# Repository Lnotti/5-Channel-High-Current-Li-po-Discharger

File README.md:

# 5 Channel High Current LiPo Storage Discharger

A PCB designed to discharge 6S LiHV battery packs to storage voltage (3.8V per cell / 22.8V total) across up to 5 independent channels simultaneously.

## Overview

Leaving LiPo packs fully charged for extended periods degrades cell chemistry over time. This board solves that by providing a dedicated, controlled way to bring packs down to storage voltage after a flying session without needing a full featured charger to do it.

Each of the 5 channels accepts a 6S pack via an XT60 connector and independently discharges it to 22.8V, cutting off automatically when the target is reached. Channels are fully isolated from each other so packs at different voltages can be discharged simultaneously without risk.

## Problems with current solutions

I have a lipo charger that doubles as a lipo discharger, but it falls short in many aspects.
- Cost ($100+)
- Only two channels
- Discharge current only 0.2A max
- Slows down immensely close to the end of discharge cycle

I also have small lipo discharger that clip onto individual packs that also fall short
- Takes 3+ hours to discharge to storage
- Only has a light to let me know that it has finished (I forget about them since they are so small)
- High leakage current
- High leakage current combined with the time taken to discharge combined with their forgettability leads to frequent overdischarging making me plug them back in to charge ruining the ease

## Status

Version 0.1.1 is a complete board redesign addressing multiple hardware issues identified during review of the 0.1.0 prototype. The revised board has been submitted for manufacture. Testing and firmware development are ongoing.

## Hardware

- STM32F103C8T6 microcontroller
- Active MOSFET load per channel with wirewound power resistors
- Buck converter and 3.3V LDO onboard power supply
- USB-C port for firmware flashing via DFU bootloader
- Active cooling via 40mm 5V fan
- Power status LED for supply rail debugging
- SWD header for live debugging
- Multiple STM32 connectivity options: USB, I2C, ST-Link, UART, DFU

## Specifications

- Input: 6S LiHV (22.8V - 26.1V)
- Channels: 5 independent
- Discharge current: approximately 1A per channel
- Target storage voltage: 22.8V (3.8V per cell)
- Connector: XT60 female PCB mount
- Board dimensions: 160 x 110mm

## Version History

### v0.1.1 — Complete Board Redesign
*Current version*

A full redesign addressing hardware errors found during schematic and layout review of v0.1.0.

**Bug fixes:**
- Corrected footprints for large wirewound power resistors which were wrong in v0.1.0
- Fixed STM32F103C8T6 footprint which was incorrect in v0.1.0
- Replaced buck converter with a higher rated part after identifying that the original selection would be insufficient for LiHV pack voltages (26.1V max vs 25.2V assumed for standard LiPo)
- Updated voltage divider resistor values (1M / 120k) to bring the ADC sense voltage within safe range for LiHV full charge voltage — previous values would have exceeded the STM32 3.3V ADC input limit at 26.1V
- Updated voltage dividers to higher values to reduce current draw, as to not discharge batteries less than their storage voltage after discharging process is complete.

**Design changes:**
- Discharge resistors repositioned to the center of the board based on thermal simulation results for improved heat distribution
- Removed per-channel RGB LEDs to simplify bring-up and reduce scope; power system debugging is now the immediate priority
- Added power rail status LED to aid debugging of the onboard supply
- Added multiple STM32 connectivity options: USB, I2C, ST-Link, UART, DFU headers
- Removed oversized battery net traces; 1A continuous current does not require large copper pours
- Redesigned discharge channels using hierarchical sheets for layout uniformity across all 5 channels and easier future edits
- General board layout cleanup and component alignment

**Known limitations:**
- RGB per-channel status LEDs removed; may be reintroduced in a later revision once core functionality is validated
- Unsure of how precise the mosfet discharge current in relation to gate voltage will be, this may create issues with precision at the end of a discharge cycle limiting speed.
- Firmware development not yet started
- Unsure of what control loop I will use to handle getting to storage voltage at a consistent current with no overshoot

---

### v0.1.0 — Initial Prototype
*First PCB submission. Multiple hardware errors identified prior to and during bring-up.*

- Initial 5-channel discharge board design
- STM32F103C8T6 microcontroller
- PCA9685 16 channel PWM driver for RGB status LEDs
- Per channel RGB status LED
- USB-C DFU bootloader
- SWD debug header
- 160 x 110mm board

**Issues identified:**
- Wrong footprints for wirewound power resistors
- Wrong STM32 footprint
- Buck converter underrated for LiHV input voltage
- Voltage divider ratio unsafe for LiHV full charge voltage on STM32 ADC
- Board layout not uniform across discharge channels

---

## Planned Revisions

- Case design with integrated fan mounting and ventilation
- Thermal testing and validation on physical hardware
- Firmware development and testing
- Potential reintroduction of per-channel RGB status LEDs
- Potential support for additional cell counts
- Further refinement based on prototype testing results

## Repository Contents

- KiCad schematic and PCB layout files
- Gerber files for manufacture
- Bill of materials

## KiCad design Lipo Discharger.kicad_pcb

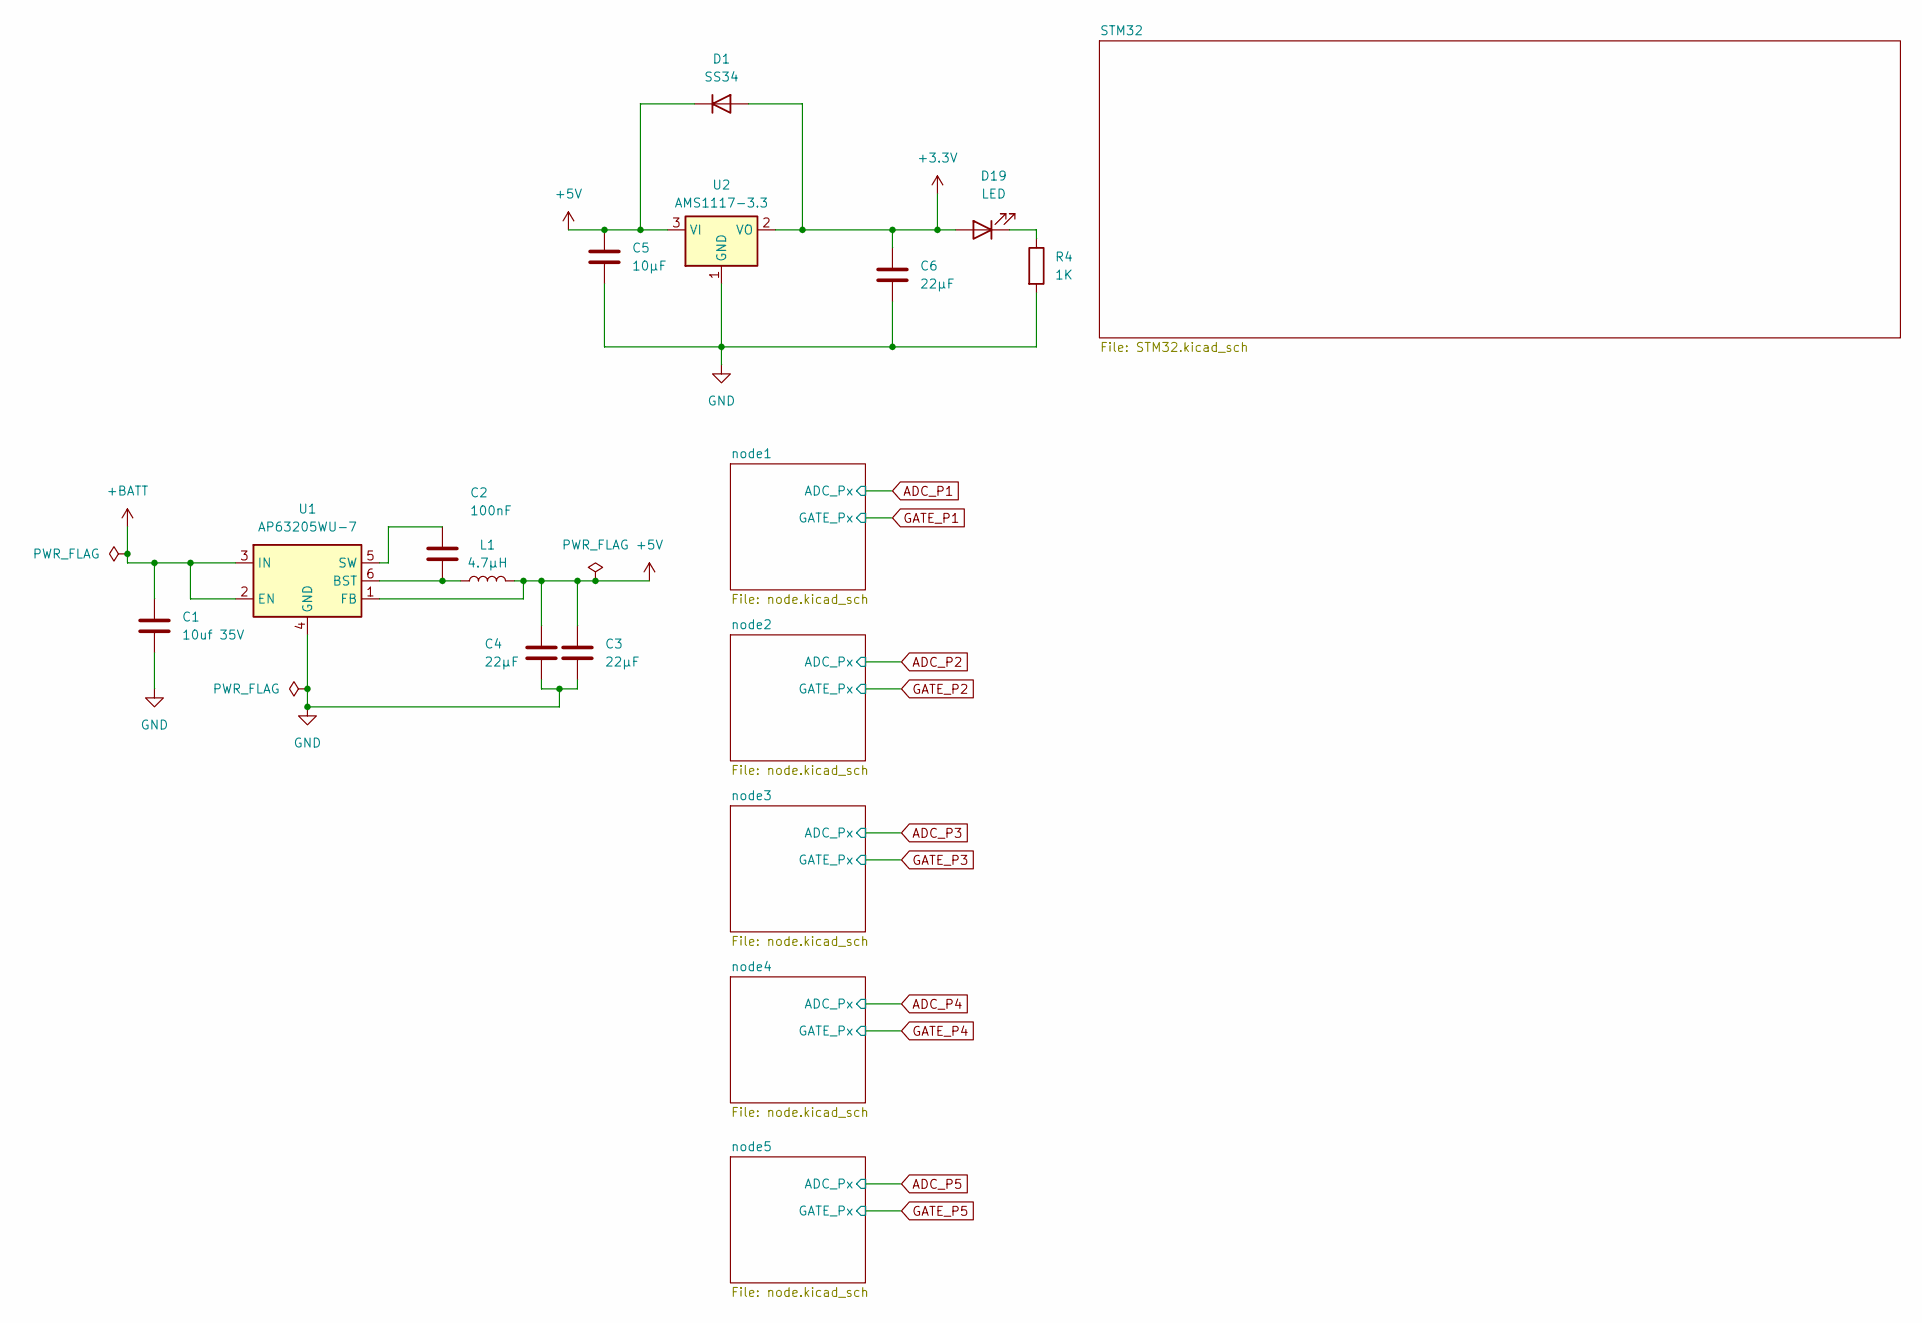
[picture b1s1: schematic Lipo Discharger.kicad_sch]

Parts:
C1: 10uf 35V; C_0805_2012Metric_Pad1.18x1.45mm_HandSolder
C2: 100nF; C_0805_2012Metric_Pad1.18x1.45mm_HandSolder
C3, C4, C6: 22µF; C_0805_2012Metric_Pad1.18x1.45mm_HandSolder
C5: 10µF; C_0805_2012Metric_Pad1.18x1.45mm_HandSolder
D1: SS34; D_SMB_Handsoldering
D19: LED; LED_2010_5025Metric_Pad1.52x2.65mm_HandSolder
L1: 4.7µH; L_7.3x7.3_H4.5
R4: 1K; R_0805_2012Metric_Pad1.20x1.40mm_HandSolder
U1: AP63205WU-7; TSOT-23-6
U2: AMS1117-3.3; SOT-223-3_TabPin2

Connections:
+3.3V: C6.1, D1.2 (A), D19.2 (A), U2.2 (VO); also elsewhere on the board
+5V: C3.1, C4.1, C5.1, D1.1 (K), L1.2, U1.1 (FB), U2.3 (VI); also elsewhere on the board
+BATT: C1.1, U1.2 (EN), U1.3 (IN); also elsewhere on the board
GND: C1.2, C3.2, C4.2, C5.2, C6.2, R4.2, U1.4 (GND), U2.1 (GND); also elsewhere on the board
unnamed: D19.1 (K), R4.1
unnamed: C2.2, L1.1, U1.6 (BST)
unnamed: C2.1, U1.5 (SW)

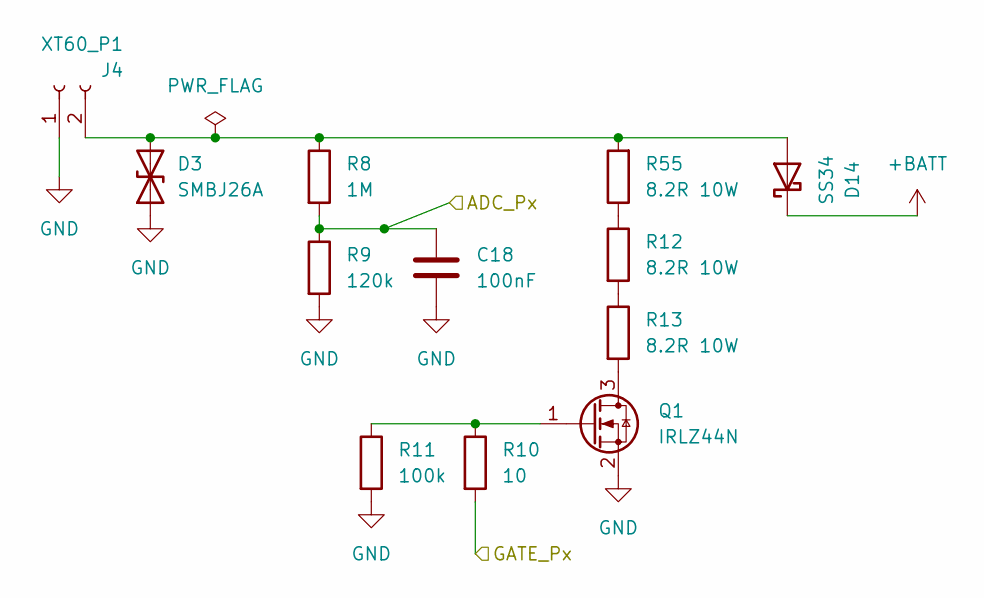
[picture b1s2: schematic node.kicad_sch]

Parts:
C18: 100nF; C_0805_2012Metric_Pad1.18x1.45mm_HandSolder
D3: SMBJ26A; D_SMB_Handsoldering
D14: SS34; D_SMA
J4: XT60_P1; AMASS_XT60PW-M_1x02_P7.20mm_Horizontal
Q1: IRLZ44N; TO-220-3_Vertical
R8: 1M; R_0805_2012Metric_Pad1.20x1.40mm_HandSolder
R9: 120k; R_0805_2012Metric_Pad1.20x1.40mm_HandSolder
R10: 10; R_0805_2012Metric_Pad1.20x1.40mm_HandSolder
R11: 100k; R_0805_2012Metric_Pad1.20x1.40mm_HandSolder
R12, R13, R55: 8.2R 10W; R_Axial_Power_L38.0mm_W6.4mm_P45.72mm

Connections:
+BATT: D14.1 (K); also elsewhere on the board
ADC_P1: C18.1, R8.2, R9.1; also elsewhere on the board
GATE_P1: R10.2; also elsewhere on the board
GND: C18.2, D3.1 (A1), J4.1, Q1.2 (S), R9.2, R11.2; also elsewhere on the board
unnamed: D3.2 (A2), D14.2 (A), J4.2, R8.1, R55.2
unnamed: Q1.3 (D), R13.2
unnamed: Q1.1 (G), R10.1, R11.1
unnamed: R12.1, R55.1
unnamed: R12.2, R13.1

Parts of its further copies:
C19, C20, C21, C22: 100nF; C_0805_2012Metric_Pad1.18x1.45mm_HandSolder
D4, D5, D6, D7: SMBJ26A; D_SMB_Handsoldering
D15, D16, D17, D18: SS34; D_SMA
J5, J6, J7, J8: XT60_P1; AMASS_XT60PW-M_1x02_P7.20mm_Horizontal
Q2, Q3, Q4, Q5: IRLZ44N; TO-220-3_Vertical
R14, R20, R26, R32: 1M; R_0805_2012Metric_Pad1.20x1.40mm_HandSolder
R15, R21, R27, R33: 120k; R_0805_2012Metric_Pad1.20x1.40mm_HandSolder
R16, R22, R28, R34: 100k; R_0805_2012Metric_Pad1.20x1.40mm_HandSolder
R17, R23, R29, R35: 10; R_0805_2012Metric_Pad1.20x1.40mm_HandSolder
R18, R19, R24, R25, R30, R31, R36, R37, R56, R57, R58, R59: 8.2R 10W; R_Axial_Power_L38.0mm_W6.4mm_P45.72mm

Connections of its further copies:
+BATT: D15.1 (K), D16.1 (K), D17.1 (K), D18.1 (K); also elsewhere on the board
ADC_P2: C19.1, R14.2, R15.1; also elsewhere on the board
ADC_P3: C20.1, R20.2, R21.1; also elsewhere on the board
ADC_P4: C21.1, R26.2, R27.1; also elsewhere on the board
ADC_P5: C22.1, R32.2, R33.1; also elsewhere on the board
GATE_P2: R17.2; also elsewhere on the board
GATE_P3: R23.2; also elsewhere on the board
GATE_P4: R29.2; also elsewhere on the board
GATE_P5: R35.2; also elsewhere on the board
GND: C19.2, C20.2, C21.2, C22.2, D4.1 (A1), D5.1 (A1), D6.1 (A1), D7.1 (A1), J5.1, J6.1, J7.1, J8.1, Q2.2 (S), Q3.2 (S), Q4.2 (S), Q5.2 (S), R15.2, R16.2, R21.2, R22.2, R27.2, R28.2, R33.2, R34.2; also elsewhere on the board
unnamed: D4.2 (A2), D15.2 (A), J5.2, R14.1, R56.2
unnamed: D5.2 (A2), D16.2 (A), J6.2, R20.1, R57.2
unnamed: D6.2 (A2), D17.2 (A), J7.2, R26.1, R58.2
unnamed: D7.2 (A2), D18.2 (A), J8.2, R32.1, R59.2
unnamed: Q2.3 (D), R19.2
unnamed: Q2.1 (G), R16.1, R17.1
unnamed: Q3.3 (D), R25.2
unnamed: Q3.1 (G), R22.1, R23.1
unnamed: Q4.3 (D), R31.2
unnamed: Q4.1 (G), R28.1, R29.1
unnamed: Q5.3 (D), R37.2
unnamed: Q5.1 (G), R34.1, R35.1
unnamed: R18.1, R56.1
unnamed: R18.2, R19.1
unnamed: R24.1, R57.1
unnamed: R24.2, R25.1
unnamed: R30.1, R58.1
unnamed: R30.2, R31.1
unnamed: R36.1, R59.1
unnamed: R36.2, R37.1

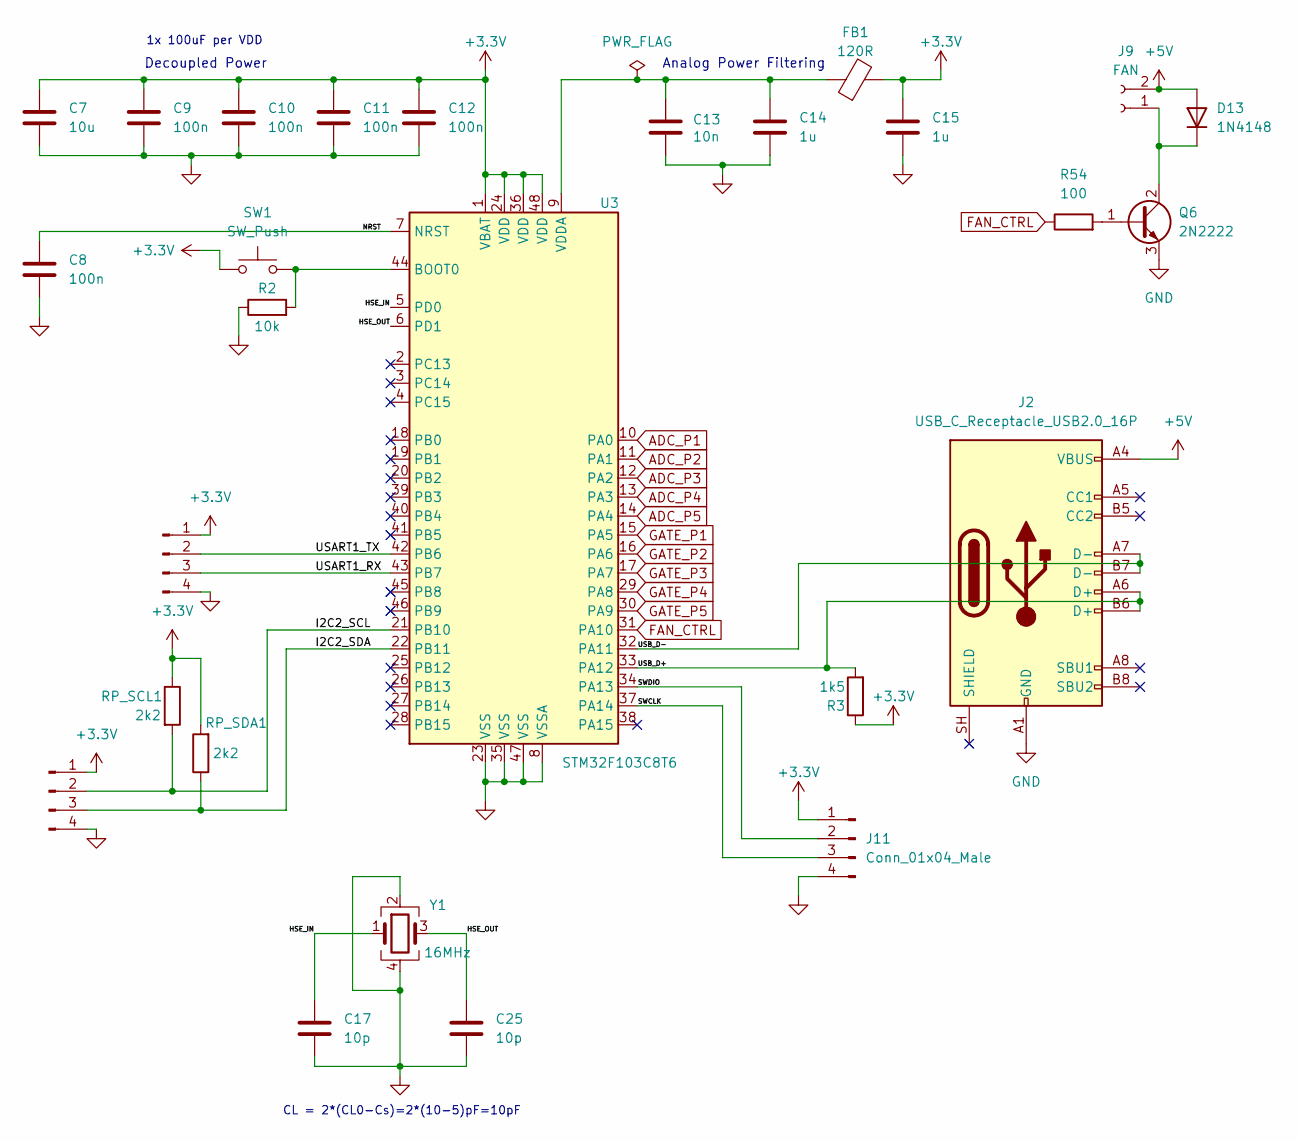
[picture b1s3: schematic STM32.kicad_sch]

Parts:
C7: 10u; C_0603_1608Metric
C8, C9, C10, C11, C12: 100n; C_0402_1005Metric
C13: 10n; C_0402_1005Metric
C14, C15: 1u; C_0402_1005Metric
C17, C25: 10p; C_0402_1005Metric
D13: 1N4148; D_DO-35_SOD27_P7.62mm_Horizontal
FB1: 120R; L_0603_1608Metric
J1, J3, J11: Conn_01x04_Male; PinHeader_1x04_P2.00mm_Vertical
J2: USB_C_Receptacle_USB2.0_16P; USB_C_Receptacle_HRO_TYPE-C-31-M-12
J9: FAN; PinHeader_1x02_P2.54mm_Vertical
Q6: 2N2222; TO-92_Inline
R2: 10k; R_0402_1005Metric
R3: 1k5; R_0402_1005Metric
R54: 100; R_0805_2012Metric_Pad1.20x1.40mm_HandSolder
RP_SCL1: 2k2; R_0402_1005Metric
RP_SDA1: 2k2; R_0402_1005Metric
SW1: SW_Push; SW_PUSH_6mm
U3: STM32F103C8T6; LQFP-48_7x7mm_P0.5mm
Y1: 16MHz; Crystal_SMD_3225-4Pin_3.2x2.5mm

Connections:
+3.3V: C7.1, C9.1, C10.1, C11.1, C12.1, C15.1, FB1.2, J1.1, J3.1, J11.1, R3.1, RP_SCL1.1, RP_SDA1.2, SW1.1, U3.1 (VBAT), U3.24 (VDD), U3.36 (VDD), U3.48 (VDD); also elsewhere on the board
+5V: D13.2 (A), J2.A4 (VBUS), J2.A9 (VBUS), J2.B4 (VBUS), J2.B9 (VBUS), J9.2; also elsewhere on the board
/STM32/HSE_IN: C17.1, U3.5 (PD0), Y1.1
/STM32/HSE_OUT: C25.1, U3.6 (PD1), Y1.3
/STM32/I2C2_SCL: J3.2, RP_SCL1.2, U3.21 (PB10); also elsewhere on the board
/STM32/I2C2_SDA: J3.3, RP_SDA1.1, U3.22 (PB11); also elsewhere on the board
/STM32/NRST: C8.1, U3.7 (NRST)
/STM32/SWCLK: J11.3, U3.37 (PA14); also elsewhere on the board
/STM32/SWDIO: J11.2, U3.34 (PA13); also elsewhere on the board
/STM32/USART1_RX: J1.3, U3.43 (PB7); also elsewhere on the board
/STM32/USART1_TX: J1.2, U3.42 (PB6); also elsewhere on the board
/STM32/USB_D+: J2.A6 (D+), J2.B6 (D+), R3.2, U3.33 (PA12)
/STM32/USB_D-: J2.A7 (D-), J2.B7 (D-), U3.32 (PA11)
ADC_P1: U3.10 (PA0); also elsewhere on the board
ADC_P2: U3.11 (PA1); also elsewhere on the board
ADC_P3: U3.12 (PA2); also elsewhere on the board
ADC_P4: U3.13 (PA3); also elsewhere on the board
ADC_P5: U3.14 (PA4); also elsewhere on the board
FAN_CTRL: R54.1, U3.31 (PA10)
GATE_P1: U3.15 (PA5); also elsewhere on the board
GATE_P2: U3.16 (PA6); also elsewhere on the board
GATE_P3: U3.17 (PA7); also elsewhere on the board
GATE_P4: U3.29 (PA8); also elsewhere on the board
GATE_P5: U3.30 (PA9); also elsewhere on the board
GND: C7.2, C8.2, C9.2, C10.2, C11.2, C12.2, C13.2, C14.2, C15.2, C17.2, C25.2, J1.4, J2.A1 (GND), J2.A12 (GND), J2.B1 (GND), J2.B12 (GND), J3.4, J11.4, Q6.3 (E), R2.1, U3.8 (VSSA), U3.23 (VSS), U3.35 (VSS), U3.47 (VSS), Y1.2, Y1.4; also elsewhere on the board
unnamed 26: D13.1 (K), J9.1, Q6.2 (C); also elsewhere on the board
unnamed: Q6.1 (B), R54.2
unnamed: R2.2, SW1.2, U3.44 (BOOT0)
unnamed: C13.1, C14.1, FB1.1, U3.9 (VDDA)

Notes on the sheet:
1x 100uF per VDD
Analog Power Filtering
Decoupled Power
CL = 2*(CL0-Cs)=2*(10-5)pF=10pF

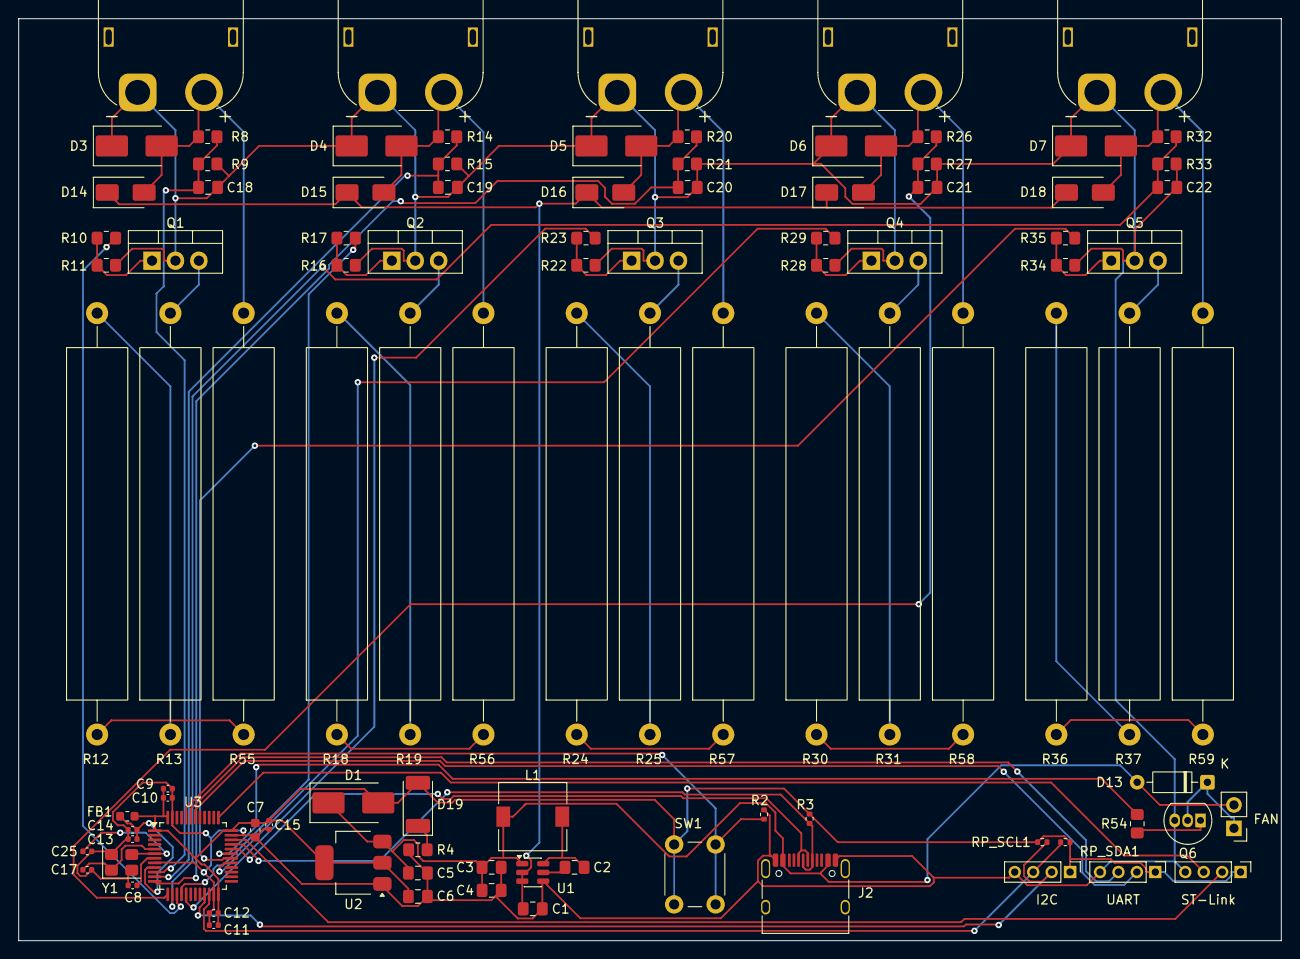
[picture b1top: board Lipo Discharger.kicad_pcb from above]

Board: 2 copper layers, 137.0 x 100.0 mm, 99 parts (0 on the bottom side), 58 nets.

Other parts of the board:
FAN: FAN; PinHeader_1x02_P2.54mm_Vertical
I2C: Conn_01x04_Male; PinHeader_1x04_P2.00mm_Vertical
ST-Link: Conn_01x04_Male; PinHeader_1x04_P2.00mm_Vertical
UART: Conn_01x04_Male; PinHeader_1x04_P2.00mm_Vertical

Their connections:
+3.3V: I2C.1, ST-Link.1, UART.1; also elsewhere on the board
+5V: FAN.2; also elsewhere on the board
/STM32/I2C2_SCL: I2C.2; also elsewhere on the board
/STM32/I2C2_SDA: I2C.3; also elsewhere on the board
/STM32/SWCLK: ST-Link.3; also elsewhere on the board
/STM32/SWDIO: ST-Link.2; also elsewhere on the board
/STM32/USART1_RX: UART.3; also elsewhere on the board
/STM32/USART1_TX: UART.2; also elsewhere on the board
GND: I2C.4, ST-Link.4, UART.4; also elsewhere on the board
unnamed 26: FAN.1; also elsewhere on the board

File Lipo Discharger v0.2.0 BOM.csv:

"Id";"Designator";"Footprint";"Quantity";"Designation";"Supplier and ref";
1;"C1";"C_0805_2012Metric_Pad1.18x1.45mm_HandSolder";1;"10uf 35V";;;
2;"C2, C18, C19, C20, C21, C22";"C_0805_2012Metric_Pad1.18x1.45mm_HandSolder";6;"100nF";;;
3;"C3, C4, C6";"C_0805_2012Metric_Pad1.18x1.45mm_HandSolder";3;"22µF";;;
4;"C5";"C_0805_2012Metric_Pad1.18x1.45mm_HandSolder";1;"10µF";;;
5;"C7";"C_0603_1608Metric";1;"10u";;;
6;"C8, C9, C10, C11, C12";"C_0402_1005Metric";5;"100n";;;
7;"C13";"C_0402_1005Metric";1;"10n";;;
8;"C14, C15";"C_0402_1005Metric";2;"1u";;;
9;"C17, C25";"C_0402_1005Metric";2;"10p";;;
10;"D1";"D_SMB_Handsoldering";1;"SS34";;;
11;"D3, D4, D5, D6, D7";"D_SMB_Handsoldering";5;"SMBJ26A";;;
12;"D13";"D_DO-35_SOD27_P7.62mm_Horizontal";1;"1N4148";;;
13;"D14, D15, D16, D17, D18";"D_SMA";5;"SS34";;;
14;"D19";"LED_2010_5025Metric_Pad1.52x2.65mm_HandSolder";1;"LED";;;
15;"FAN";"PinHeader_1x02_P2.54mm_Vertical";1;"FAN";;;
16;"FB1";"L_0603_1608Metric";1;"120R";;;
17;"I2C, ST-Link, UART";"PinHeader_1x04_P2.00mm_Vertical";3;"Conn_01x04_Male";;;
18;"J2";"USB_C_Receptacle_HRO_TYPE-C-31-M-12";1;"USB_C_Receptacle_USB2.0_16P";;;
19;"J4, J5, J6, J7, J8";"AMASS_XT60PW-M_1x02_P7.20mm_Horizontal";5;"XT60_P1";;;
20;"L1";"L_7.3x7.3_H4.5";1;"4.7µH";;;
21;"Q1, Q2, Q3, Q4, Q5";"TO-220-3_Vertical";5;"IRLZ44N";;;
22;"Q6";"TO-92_Inline";1;"2N2222";;;
23;"R2";"R_0402_1005Metric";1;"10k";;;
24;"R3";"R_0402_1005Metric";1;"1k5";;;
25;"R4";"R_0805_2012Metric_Pad1.20x1.40mm_HandSolder";1;"1K";;;
26;"R8, R14, R20, R26, R32";"R_0805_2012Metric_Pad1.20x1.40mm_HandSolder";5;"1M";;;
27;"R9, R15, R21, R27, R33";"R_0805_2012Metric_Pad1.20x1.40mm_HandSolder";5;"120k";;;
28;"R10, R17, R23, R29, R35";"R_0805_2012Metric_Pad1.20x1.40mm_HandSolder";5;"10";;;
29;"R11, R16, R22, R28, R34";"R_0805_2012Metric_Pad1.20x1.40mm_HandSolder";5;"100k";;;
30;"R12, R13, R18, R19, R24, R25, R30, R31, R36, R37, R55, R56, R57, R58, R59";"R_Axial_Power_L38.0mm_W6.4mm_P45.72mm";15;"8.2R 10W";;;
31;"R54";"R_0805_2012Metric_Pad1.20x1.40mm_HandSolder";1;"100";;;
32;"RP_SCL1, RP_SDA1";"R_0402_1005Metric";2;"2k2";;;
33;"SW1";"SW_PUSH_6mm";1;"SW_Push";;;
34;"U1";"TSOT-23-6";1;"AP63205WU-7";;;
35;"U2";"SOT-223-3_TabPin2";1;"AMS1117-3.3";;;
36;"U3";"LQFP-48_7x7mm_P0.5mm";1;"STM32F103C8T6";;;
37;"Y1";"Crystal_SMD_3225-4Pin_3.2x2.5mm";1;"16MHz";;;

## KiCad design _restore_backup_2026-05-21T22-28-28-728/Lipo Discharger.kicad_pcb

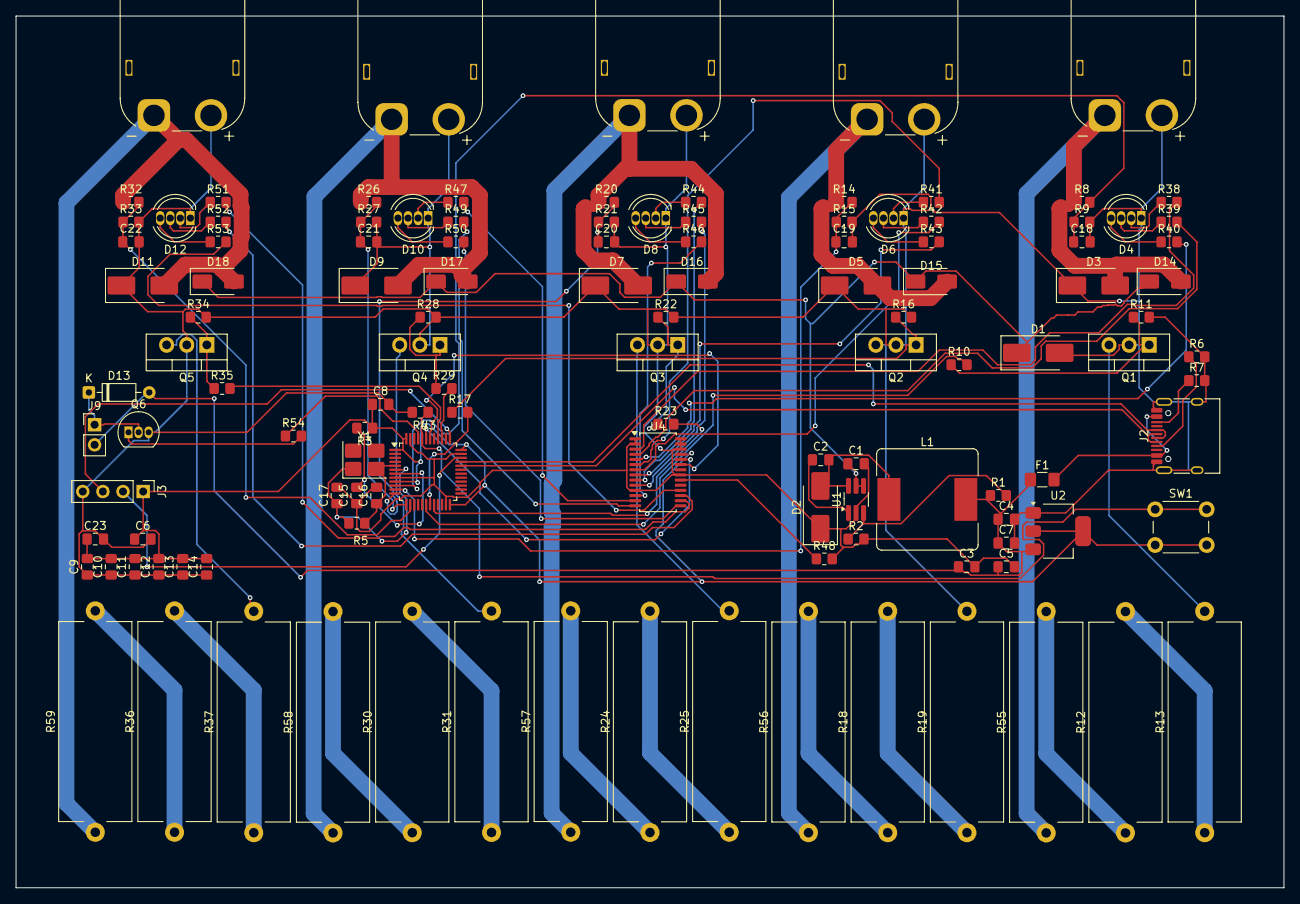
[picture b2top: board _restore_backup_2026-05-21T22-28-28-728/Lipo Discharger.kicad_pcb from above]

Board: 2 copper layers, 160.0 x 110.0 mm, 122 parts (0 on the bottom side), 89 nets.

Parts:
C1: 10uf 35V; C_0805_2012Metric_Pad1.18x1.45mm_HandSolder
C2, C7, C8, C9, C10, C11, C12, C15, C18, C19, C20, C21, C22, C23: 100nF; C_0805_2012Metric_Pad1.18x1.45mm_HandSolder
C3, C4: 22uF 10V; C_0805_2012Metric_Pad1.18x1.45mm_HandSolder
C5, C6: 10uF; C_0805_2012Metric_Pad1.18x1.45mm_HandSolder
C13: 1uF; C_0805_2012Metric_Pad1.18x1.45mm_HandSolder
C14: 10nF; C_0805_2012Metric_Pad1.18x1.45mm_HandSolder
C16, C17: 20pF; C_0805_2012Metric_Pad1.18x1.45mm_HandSolder
D1: D_TVS; D_SMB_Handsoldering
D2: SS34; D_SMB_Handsoldering
D3, D5, D7, D9, D11: SMBJ26A; D_SMB_Handsoldering
D4, D6, D8, D10, D12: LED_KRGB; LED_D5.0mm-4_RGB
D13: 1N4148; D_DO-35_SOD27_P7.62mm_Horizontal
D14, D15, D16, D17, D18: SS34; D_SMA
F1: Polyfuse; Fuse_1206_3216Metric_Pad1.42x1.75mm_HandSolder
J2: USB_C_Receptacle_USB2.0_16P; USB_C_Receptacle_HRO_TYPE-C-31-M-12
J3: SWD; PinHeader_1x04_P2.54mm_Vertical
J4: XT60_P1; AMASS_XT60PW-M_1x02_P7.20mm_Horizontal
J5: XT60_P2; AMASS_XT60PW-M_1x02_P7.20mm_Horizontal
J6: XT60_P3; AMASS_XT60PW-M_1x02_P7.20mm_Horizontal
J7: XT60_P4; AMASS_XT60PW-M_1x02_P7.20mm_Horizontal
J8: XT60_P5; AMASS_XT60PW-M_1x02_P7.20mm_Horizontal
J9: FAN; PinHeader_1x02_P2.54mm_Vertical
L1: 22uH; L_Bourns_SRR1260
Q1, Q2, Q3, Q4, Q5: IRLZ44N; TO-220-3_Vertical
Q6: 2N2222; TO-92_Inline
R1, R8, R11, R14, R16, R20, R22, R26, R28, R32, R34: 100k; R_0805_2012Metric_Pad1.20x1.40mm_HandSolder
R2: 20k; R_0805_2012Metric_Pad1.20x1.40mm_HandSolder
R3, R4, R48: 10k; R_0805_2012Metric_Pad1.20x1.40mm_HandSolder
R5: 1M; R_0805_2012Metric_Pad1.20x1.40mm_HandSolder
R6, R7: 5.1k; R_0805_2012Metric_Pad1.20x1.40mm_HandSolder
R9, R15, R21, R27, R33: 15k; R_0805_2012Metric_Pad1.20x1.40mm_HandSolder
R10, R17, R23, R29, R35: 10; R_0805_2012Metric_Pad1.20x1.40mm_HandSolder
R12, R13, R18, R19, R24, R25, R30, R31, R36, R37, R55, R56, R57, R58, R59: 8.2R 10W; R_Axial_Power_L25.0mm_W9.0mm_P27.94mm
R38, R41, R44, R47, R51: 68; R_0805_2012Metric_Pad1.20x1.40mm_HandSolder
R39, R40, R42, R43, R45, R46, R49, R50, R52, R53: 22; R_0805_2012Metric_Pad1.20x1.40mm_HandSolder
R54: 100; R_0805_2012Metric_Pad1.20x1.40mm_HandSolder
SW1: BOOT0_BTN; SW_PUSH_6mm
U1: MP2359DJ-LF-Z; TSOT-23-6_HandSoldering
U2: AMS1117-3.3; SOT-223-3_TabPin2
U3: STM32F103C8Tx; LQFP-48_7x7mm_P0.5mm
U4: PCA9685BS; TSSOP-28_4.4x9.7mm_P0.65mm
Y1: 8MHz; Crystal_SMD_3225-4Pin_3.2x2.5mm_HandSoldering

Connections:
+3.3V: C6.1, C8.1, C9.2, C10.2, C11.2, C12.2, C13.2, C14.2, C23.1, J3.1, R3.1, SW1.2, U2.2 (VO), U3.1 (VBAT), U3.9 (VDDA), U3.24 (VDD), U3.36 (VDD), U3.48 (VDD), U4.25 (VDD)
+5V: C3.1, C4.1, C5.1, C7.1, D13.2 (A), F1.1, J9.2, L1.2, R1.1, U2.3 (VI)
+BATT: C1.1, D1.1 (A1), D14.1 (K), D15.1 (K), D16.1 (K), D17.1 (K), D18.1 (K), U1.4 (EN), U1.5 (IN)
-BATT: C1.2, C3.2, C4.2, C5.2, C6.2, C7.2, C8.2, C9.1, C10.1, C11.1, C12.1, C13.1, C14.1, C15.1, C16.2, C17.2, C18.2, C19.2, C20.2, C21.2, C22.2, C23.2, D1.2 (A2), D2.1 (K), D3.1 (A1), D4.1 (K), D5.1 (A1), D6.1 (K), D7.1 (A1), D8.1 (K), D9.1 (A1), D10.1 (K), D11.1 (A1), D12.1 (K), J2.A1 (GND), J2.A12 (GND), J2.B1 (GND), J2.B12 (GND), J2.SH (SHIELD), J3.4, J4.2, J5.2, J6.2, J7.2, J8.2, Q1.2 (S), Q2.2 (S), Q3.2 (S), Q4.2 (S), Q5.2 (S), Q6.3 (E), R2.2, R4.2, R6.2, R7.2, R9.2, R11.2, R15.2, R16.2, R21.2, R22.2, R27.2, R28.2, R33.2, R34.2, R48.2, U1.2 (GND), U2.1 (GND), U3.8 (VSSA), U3.23 (VSS), U3.35 (VSS), U3.47 (VSS), U4.1 (A3), U4.2 (A4), U4.11 (VSS), U4.21 (A5), U4.26 (A0), U4.27 (A1), U4.28 (A2)
ADC_P1: C18.1, R8.2, R9.1, U3.10 (PA0)
ADC_P2: C19.1, R14.2, R15.1, U3.11 (PA1)
ADC_P3: C20.1, R20.2, R21.1, U3.12 (PA2)
ADC_P4: C21.1, R26.2, R27.1, U3.13 (PA3)
ADC_P5: C22.1, R32.2, R33.1, U3.14 (PA4)
FAN_CTRL: R54.1, U3.45 (PB8)
GATE_P1: R10.2, U3.18 (PB0)
GATE_P2: R17.2, U3.19 (PB1)
GATE_P3: R23.2, U3.20 (PB2)
GATE_P4: R29.2, U3.39 (PB3)
GATE_P5: R35.2, U3.40 (PB4)
I2C_SCL: U3.42 (PB6), U4.23 (SCL)
I2C_SDA: U3.43 (PB7), U4.24 (SDA)
LED_P1_B: R40.2, U4.5 (LED2)
LED_P1_G: R39.2, U4.4 (LED1)
LED_P1_R: R38.2, U4.3 (LED0)
LED_P2_B: R43.2, U4.8 (LED5)
LED_P2_G: R42.2, U4.7 (LED4)
LED_P2_R: R41.2, U4.6 (LED3)
LED_P3_B: R46.2, U4.12 (LED8)
LED_P3_G: R45.2, U4.10 (LED7)
LED_P3_R: R44.2, U4.9 (LED6)
LED_P4_B: R50.2, U4.15 (LED11)
LED_P4_G: R49.2, U4.14 (LED10)
LED_P4_R: R47.2, U4.13 (LED9)
LED_P5_B: R53.2, U4.18 (LED14)
LED_P5_G: R52.2, U4.17 (LED13)
LED_P5_R: R51.2, U4.16 (LED12)
unnamed: C2.2, D2.2 (A), L1.1, U1.6 (SW)
unnamed: D4.4 (BA), R40.1
unnamed: D4.3 (GA), R39.1
unnamed: D4.2 (RA), R38.1
unnamed: D6.4 (BA), R43.1
unnamed: D6.3 (GA), R42.1
unnamed: D6.2 (RA), R41.1
unnamed: D8.4 (BA), R46.1
unnamed: D8.3 (GA), R45.1
unnamed: D8.2 (RA), R44.1
unnamed: D10.4 (BA), R50.1
unnamed: D10.3 (GA), R49.1
unnamed: D10.2 (RA), R47.1
unnamed: D12.4 (BA), R53.1
unnamed: D12.3 (GA), R52.1
unnamed: D12.2 (RA), R51.1
unnamed: D13.1 (K), J9.1, Q6.2 (C)
unnamed: F1.2, J2.A4 (VBUS), J2.A9 (VBUS), J2.B4 (VBUS), J2.B9 (VBUS)
unnamed: J2.A5 (CC1), R6.1
unnamed: J2.B5 (CC2), R7.1
unnamed: J3.2, U3.34 (PA13)
unnamed: J3.3, U3.37 (PA14)
unnamed: Q1.3 (D), R13.2
unnamed: Q1.1 (G), R10.1, R11.1
unnamed: Q2.3 (D), R19.2
unnamed: Q2.1 (G), R16.1, R17.1
unnamed: Q3.3 (D), R25.2
unnamed: Q3.1 (G), R22.1, R23.1
unnamed: Q4.3 (D), R31.2
unnamed: Q4.1 (G), R28.1, R29.1
unnamed: Q5.3 (D), R37.2
unnamed: Q5.1 (G), R34.1, R35.1
unnamed: Q6.1 (B), R54.2
unnamed: R12.1, R55.2
unnamed: R12.2, R13.1
unnamed: R18.1, R56.2
unnamed: R18.2, R19.1
unnamed: R24.1, R57.2
unnamed: R24.2, R25.1
unnamed: R30.1, R58.2
unnamed: R30.2, R31.1
unnamed: R36.1, R59.2
unnamed: R36.2, R37.1
unnamed: C2.1, U1.1 (BST)
unnamed: R1.2, R2.1, U1.3 (FB)
unnamed: R4.1, SW1.1, U3.44 (BOOT0)
unnamed: C15.2, R3.2, U3.7 (NRST)
unnamed: C16.1, R5.1, U3.5 (PD0), Y1.2
unnamed: C17.1, R5.2, U3.6 (PD1), Y1.1
unnamed: R48.1, U4.20 (~OE)
USB_DM: J2.A7 (D-), J2.B7 (D-), U3.32 (PA11)
USB_DP: J2.A6 (D+), J2.B6 (D+), U3.33 (PA12)
VBAT_P1: D3.2 (A2), D14.2 (A), J4.1, R8.1, R55.1
VBAT_P2: D5.2 (A2), D15.2 (A), J5.1, R14.1, R56.1
VBAT_P3: D7.2 (A2), D16.2 (A), J6.1, R20.1, R57.1
VBAT_P4: D9.2 (A2), D17.2 (A), J7.1, R26.1, R58.1
VBAT_P5: D11.2 (A2), D18.2 (A), J8.1, R32.1, R59.1

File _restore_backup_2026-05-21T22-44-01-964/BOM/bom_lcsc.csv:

"Id","Designator","Footprint","Quantity","Designation"
1,"C1","C_0805_2012Metric",1,"10uF 35V"
2,"C2,C7,C8,C9,C10,C11,C12,C15,C18,C19,C20,C21,C22,C23","C_0805_2012Metric",14,"100nF"
3,"C3,C4","C_0805_2012Metric",2,"22uF 10V"
4,"C5,C6","C_0805_2012Metric",2,"10uF"
5,"C13","C_0805_2012Metric",1,"1uF"
6,"C14","C_0805_2012Metric",1,"10nF"
7,"C16,C17","C_0805_2012Metric",2,"20pF"
8,"D1","D_SMB",1,"SMBJ26A"
9,"D2","D_SMB",1,"SS34"
10,"D3,D5,D7,D9,D11","D_SMB",5,"SMBJ26A"
11,"D4,D6,D8,D10,D12","LED_D5.0mm_RGB",5,"RGB LED Common Cathode 5mm"
12,"D13","D_DO-35",1,"1N4148"
13,"D14,D15,D16,D17,D18","D_SMA",5,"SS34"
14,"F1","Fuse_1206",1,"Polyfuse 500mA"
15,"J2","USB_C_Receptacle",1,"USB-C Receptacle 16P"
16,"J3","PinHeader_1x04_P2.54mm",1,"Pin Header 1x4 2.54mm"
17,"J4,J5,J6,J7,J8","AMASS_XT60-F",5,"XT60 Female PCB Mount"
18,"J9","PinHeader_1x02_P2.54mm",1,"Pin Header 1x2 2.54mm"
19,"L1","L_Bourns_SRR1260",1,"22uH SRR1260"
20,"Q1,Q2,Q3,Q4,Q5","TO-220-3",5,"IRLZ44NPBF"
21,"Q6","TO-92",1,"2N2222"
22,"R1,R8,R11,R14,R16,R20,R22,R26,R28,R32,R34","R_0805",11,"100k 1%"
23,"R2","R_0805",1,"20k 1%"
24,"R3,R4,R48","R_0805",3,"10k"
25,"R5","R_0805",1,"1M"
26,"R6,R7","R_0805",2,"5.1k"
27,"R9,R15,R21,R27,R33","R_0805",5,"15k 1%"
28,"R10,R17,R23,R29,R35","R_0805",5,"10R"
29,"R12,R13,R18,R19,R24,R25,R30,R31,R36,R37,R55,R56,R57,R58,R59","R_Axial_Power",15,"8.2R 10W"
30,"R38,R41,R44,R47,R51","R_0805",5,"68R"
31,"R39,R40,R42,R43,R45,R46,R49,R50,R52,R53","R_0805",10,"22R"
32,"R54","R_0805",1,"100R"
33,"SW1","SW_PUSH_6mm",1,"Tactile Switch 6mm"
34,"U1","TSOT-23-6",1,"MP2359DJ-LF-Z"
35,"U2","SOT-223-3",1,"AMS1117-3.3"
36,"U3","LQFP-48",1,"STM32F103C8T6"
37,"U4","QFN-28",1,"PCA9685BS"
38,"Y1","Crystal_SMD_3225-4Pin",1,"8MHz Crystal"

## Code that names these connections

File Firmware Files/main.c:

/* =============================================================================
 * main.c — LiPo Storage Discharger
 * Target : STM32F103C8T6 @ 72MHz
 * Toolchain: STM32CubeIDE + HAL
 *
 * CubeMX peripheral configuration summary:
 *   ADC1  — Scan mode, 5 channels (IN0–IN4 = PA0–PA4), software trigger,
 *            continuous conversion OFF (we trigger manually per port)
 *   I2C1  — Standard mode 100kHz, PB6=SCL, PB7=SDA
 *   GPIO  — PB0/1/3/4/8 push-pull outputs (gates)
 *            PA5 push-pull output (fan)
 *            PA11/PA12 USB (handled by bootloader, no init needed in app)
 * =============================================================================
 */

#include "main.h"

/* ---------------------------------------------------------------------------
 * HAL handles — defined here, extern'd in main.h
 * ---------------------------------------------------------------------------*/
ADC_HandleTypeDef  hadc1;
I2C_HandleTypeDef  hi2c1;

/* ===========================================================================
 * main()
 * ===========================================================================*/
int main(void)
{
    HAL_Init();
    SystemClock_Config();   /* 72 MHz from HSE via PLL */

    MX_GPIO_Init();
    MX_ADC1_Init();
    MX_I2C1_Init();

    /* Run ADC self-calibration — mandatory on F1 for accurate readings */
    HAL_ADCEx_Calibration_Start(&hadc1);

    App_Run();   /* Never returns */
}

/* ===========================================================================
 * SystemClock_Config
 * 72 MHz: HSE 8MHz → PLL x9
 * AHB/APB2 = 72MHz, APB1 = 36MHz
 * ADC clock = PCLK2/6 = 12MHz  (max 14MHz)
 * ===========================================================================*/
void SystemClock_Config(void)
{
    RCC_OscInitTypeDef osc = {0};
    RCC_ClkInitTypeDef clk = {0};
    RCC_PeriphCLKInitTypeDef periph = {0};

    osc.OscillatorType      = RCC_OSCILLATORTYPE_HSE;
    osc.HSEState            = RCC_HSE_ON;
    osc.HSEPredivValue      = RCC_HSE_PREDIV_DIV1;
    osc.PLL.PLLState        = RCC_PLL_ON;
    osc.PLL.PLLSource       = RCC_PLLSOURCE_HSE;
    osc.PLL.PLLMUL          = RCC_PLL_MUL9;
    HAL_RCC_OscConfig(&osc);

    clk.ClockType           = RCC_CLOCKTYPE_HCLK | RCC_CLOCKTYPE_SYSCLK
                            | RCC_CLOCKTYPE_PCLK1 | RCC_CLOCKTYPE_PCLK2;
    clk.SYSCLKSource        = RCC_SYSCLKSOURCE_PLLCLK;
    clk.AHBCLKDivider       = RCC_SYSCLK_DIV1;
    clk.APB1CLKDivider      = RCC_HCLK_DIV2;   /* 36 MHz max for APB1 */
    clk.APB2CLKDivider      = RCC_HCLK_DIV1;   /* 72 MHz */
    HAL_RCC_ClockConfig(&clk, FLASH_LATENCY_2);

    periph.PeriphClockSelection = RCC_PERIPHCLK_ADC;
    periph.AdcClockSelection    = RCC_ADCPCLK2_DIV6;   /* 12 MHz */
    HAL_RCCEx_PeriphCLKConfig(&periph);
}

/* ===========================================================================
 * MX_GPIO_Init
 * Gate outputs: PB0, PB1, PB3, PB4, PB8 — push-pull, default LOW
 * Fan output:   PA5                       — push-pull, default LOW
 * ADC inputs:   PA0–PA4 are configured as analog by MX_ADC1_Init
 * ===========================================================================*/
static void MX_GPIO_Init(void)
{
    GPIO_InitTypeDef gpio = {0};

    __HAL_RCC_GPIOA_CLK_ENABLE();
    __HAL_RCC_GPIOB_CLK_ENABLE();

    /* --- Gate outputs on GPIOB --- */
    HAL_GPIO_WritePin(GATE_PORT,
                      GATE1_PIN | GATE2_PIN | GATE3_PIN | GATE4_PIN | GATE5_PIN,
                      GPIO_PIN_RESET);

    gpio.Pin   = GATE1_PIN | GATE2_PIN | GATE3_PIN | GATE4_PIN | GATE5_PIN;
    gpio.Mode  = GPIO_MODE_OUTPUT_PP;
    gpio.Speed = GPIO_SPEED_FREQ_LOW;
    gpio.Pull  = GPIO_NOPULL;
    HAL_GPIO_Init(GATE_PORT, &gpio);

    /* --- Fan output on GPIOA --- */
    HAL_GPIO_WritePin(FAN_PORT, FAN_PIN, GPIO_PIN_RESET);

    gpio.Pin   = FAN_PIN;
    gpio.Mode  = GPIO_MODE_OUTPUT_PP;
    gpio.Speed = GPIO_SPEED_FREQ_LOW;
    gpio.Pull  = GPIO_NOPULL;
    HAL_GPIO_Init(FAN_PORT, &gpio);
}

/* ===========================================================================
 * MX_ADC1_Init
 * Scan mode OFF — we convert one channel at a time per port.
 * Channels IN0–IN4 (PA0–PA4).
 * We reconfigure the channel rank before each conversion in app.c.
 * ===========================================================================*/
static void MX_ADC1_Init(void)
{
    __HAL_RCC_ADC1_CLK_ENABLE();
    __HAL_RCC_GPIOA_CLK_ENABLE();

    /* Configure PA0–PA4 as analog inputs */
    GPIO_InitTypeDef gpio = {0};
    gpio.Pin  = GPIO_PIN_0 | GPIO_PIN_1 | GPIO_PIN_2 | GPIO_PIN_3 | GPIO_PIN_4;
    gpio.Mode = GPIO_MODE_ANALOG;
    HAL_GPIO_Init(GPIOA, &gpio);

    hadc1.Instance                   = ADC1;
    hadc1.Init.ScanConvMode          = ADC_SCAN_DISABLE;  /* Single channel per call */
    hadc1.Init.ContinuousConvMode    = DISABLE;
    hadc1.Init.DiscontinuousConvMode = DISABLE;
    hadc1.Init.ExternalTrigConv      = ADC_SOFTWARE_START;
    hadc1.Init.DataAlign             = ADC_DATAALIGN_RIGHT;
    hadc1.Init.NbrOfConversion       = 1;
    HAL_ADC_Init(&hadc1);
}

/* ===========================================================================
 * MX_I2C1_Init
 * Standard mode, 100 kHz, PB6=SCL, PB7=SDA
 * ===========================================================================*/
static void MX_I2C1_Init(void)
{
    __HAL_RCC_I2C1_CLK_ENABLE();
    __HAL_RCC_GPIOB_CLK_ENABLE();

    /* PB6 SCL, PB7 SDA — alternate function open-drain */
    GPIO_InitTypeDef gpio = {0};
    gpio.Pin   = GPIO_PIN_6 | GPIO_PIN_7;
    gpio.Mode  = GPIO_MODE_AF_OD;
    gpio.Speed = GPIO_SPEED_FREQ_HIGH;
    HAL_GPIO_Init(GPIOB, &gpio);

    hi2c1.Instance             = I2C1;
    hi2c1.Init.ClockSpeed      = 100000;
    hi2c1.Init.DutyCycle       = I2C_DUTYCYCLE_2;
    hi2c1.Init.OwnAddress1     = 0;
    hi2c1.Init.AddressingMode  = I2C_ADDRESSINGMODE_7BIT;
    hi2c1.Init.DualAddressMode = I2C_DUALADDRESS_DISABLE;
    hi2c1.Init.GeneralCallMode = I2C_GENERALCALL_DISABLE;
    hi2c1.Init.NoStretchMode   = I2C_NOSTRETCH_DISABLE;
    HAL_I2C_Init(&hi2c1);
}

/* ===========================================================================
 * HAL_MspInit — called by HAL_Init()
 * ===========================================================================*/
void HAL_MspInit(void)
{
    __HAL_RCC_AFIO_CLK_ENABLE();
    __HAL_RCC_PWR_CLK_ENABLE();

    /* Disable JTAG, keep SWD — frees PB3, PB4 for GPIO use as gate pins */
    __HAL_AFIO_REMAP_SWJ_NOJTAG();
}

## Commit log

2026-05-29 Initial commit - Lipo storage discharger PCB
2026-05-29 Added Readme
2026-05-29 Add project note about risks and personal use
    Added a note regarding the project's status and usage.
2026-05-29 Fix formatting of project note in README
2026-05-29 Renamed Files
2026-06-07 Complete board redesign
2026-06-07 Updated README to include design changes
2026-06-11 Before autorouting backup
2026-06-17 Document problems with current lipo discharging solutions
    Added section on problems with current lipo discharging solutions, detailing shortcomings and issues.
2026-06-17 Document issues with existing lipo charging solutions
    Added a section discussing problems with current lipo charger and discharger solutions.
2026-06-17 V0.2.0 after sending to manufacturing
2026-06-17 V0.2.0 After Saving
2026-06-17 Added BOM to add to release
